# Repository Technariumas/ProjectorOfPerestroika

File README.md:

# ProjectorOfPerestroika
A wifi controlled old soviet flash light - a prop for a movie

To recreate:
 * Install ESP Arduino core (Tools/Board/Boards Manager...)
 * Install [Arduino ESP8266 filesystem uploader](https://github.com/esp8266/arduino-esp8266fs-plugin)

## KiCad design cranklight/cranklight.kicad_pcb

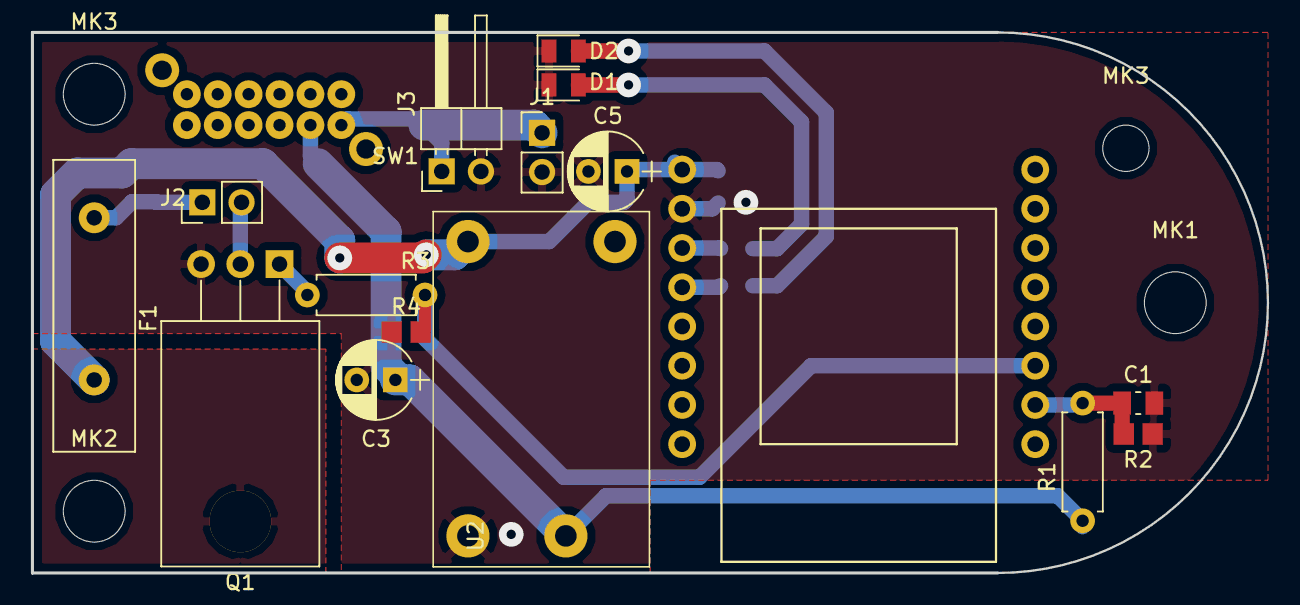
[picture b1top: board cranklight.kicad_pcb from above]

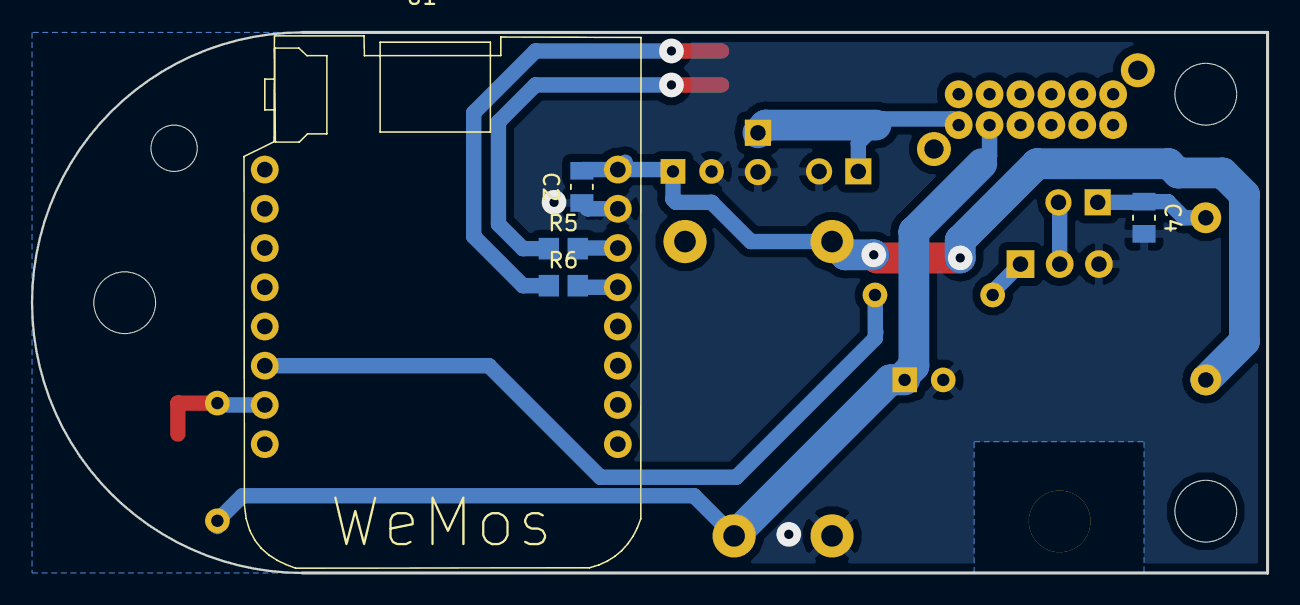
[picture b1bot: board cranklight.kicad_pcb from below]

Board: 2 copper layers, 80.0 x 35.0 mm, 25 parts (5 on the bottom side), 13 nets.

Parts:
C1, C2, C4: 1u; C_0805_2012Metric_Pad1.15x1.50mm_HandSolder
C3, C5: CP; CP_Radial_D5.0mm_P2.50mm
D1: GREEN; LED_0805_2012Metric
D2: RED; LED_0805_2012Metric
F1: Polyfuse; Fuse_Littelfuse-LVR100
J1: Battery; Pin_Header_Straight_1x02_Pitch2.54mm
J2: Bulb socket; Pin_Header_Straight_1x02_Pitch2.54mm
J3: Charge; Pin_Header_Angled_1x02_Pitch2.54mm
MK1, MK2, MK3, MK3#2: Mounting_Hole; MountingHole_3.7mm
Q1: Q_NMOS_GDS; TO-220-3_Horizontal
R1: 300k; R_Axial_DIN0207_L6.3mm_D2.5mm_P7.62mm_Horizontal
R2, R4: 100k; R_0805_2012Metric_Pad1.33x1.40mm_HandSolder
R3: 160; R_Axial_DIN0207_L6.3mm_D2.5mm_P7.62mm_Horizontal
R5, R6: 1k; R_0805_2012Metric_Pad1.33x1.40mm_HandSolder
SW1: SW_4PDT; 4PDT
U1: WeMos_mini; D1_mini_board
U2: PTN04050CAD; PTN04050

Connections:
+5V: C2.1, C5.1, F1.2, U1.1, U2.4
+BATT: J1.1, J3.1, SW1.12
GND: C1.2, C2.2, C3.2, C4.2, C5.2, D1.1, D2.1, J1.2, J3.2, Q1.3, R2.1, R4.1, U1.2, U2.1
unnamed: C1.1, R1.1, R2.2, U1.10
unnamed: C4.1, F1.1, J2.1
unnamed: D1.2, R5.1
unnamed: D2.2, R6.1
unnamed: J2.2, Q1.2
unnamed: Q1.1, R3.1
unnamed: R3.2, R4.2, U1.11
unnamed: R5.2, U1.3
unnamed: R6.2, U1.4
VCC: C3.1, R1.2, SW1.11, U2.2

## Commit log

2018-03-19 Initial commit, everything works
2018-03-19 Add some documentation about tools
2018-05-02 blink version for demo, files reshuffled
2018-05-02 Preheat after startup to avoid overstressing the battery (cold bulb resistance is very low, turning it fully on will cause battery protection circuit to hickup). Consider leaving on preheat in the lo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
2018-05-22 before state machine, three buttons
2018-05-22 state machine, enabled controls
2018-05-22 with blink rate param
2018-06-11 Add board files for small cranklight
2018-06-18 Add fixes: move PTC, add charging connector, use switch as a simple switch
2018-06-18 Add a simple test script for cranklight
2018-06-26 low battery warning
2018-06-26 D1 pin
2018-06-27 separate file for cranklight, simulated data
2018-06-27 separate sources, file reshuffle
2018-06-27 attempt to read from file
2018-06-27 play/pause/off
2018-06-27 pseudorandom sequences for pause and off cases
2018-06-28 rescaled analogwrite
2018-06-28 Voltage level, min brightness control, before adding random delay
2018-06-29 randomizer
2018-06-29 random blinking params
2018-06-29 setting load via JSON
2018-06-29 write to SPIFFS via JSON, test
2018-06-29 save and load presets
2018-06-30 before send/receive settings via JSON
2018-06-30 preset loading
2018-07-02 battery voltage indicator, websocket connection alert
2018-07-02 WIFI ssid works, failed due to short password
2018-07-03 Don't try to connect to WIFI as we are AP
2018-07-03 Add indication LEDS, add indication upon WiFi connect/disconnect
2018-07-03 flashing, voltage read test
2018-07-03 Some defensive coding - avoid creating objects and variables inside of functions to avoid working the stack and potentially allocating heap
2018-07-03 WiFi settings file
2018-07-03 More on defensive coding - reuse JsonBuffers as much as possible, remove one more dynamic buffer usage, load settings upon websocket connect, load settings upon system start
2018-07-03 Revert "Merge branch 'master' of github.com:Technariumas/ProjectorOfPerestroika"
    This reverts commit 15df6aaded9b8dc48269cf031f87443d8a172d73, reversing
    changes made to db87b0c735bae324813759881bcc5720fb8c6f46.
2018-07-03 no digitalWrite, lots of prints
2018-07-03 Add WEBSOCKETS_SERVER_CLIENT_MAX def as master of websockets lib allows to define it outside
2018-07-03 load WiFi settings from file
2018-07-03 sensible settings, CSS for tablet/mobile
2018-07-03 less Serial.print
2018-07-03 copy paste from cranklight, before rewriting
2018-07-03 JS error, voltage vs. val, check
2018-07-03 large flashlight, works
2018-07-03 fixed dimmer preset
2018-07-03 PWM duty cycle scaling
2018-07-04 voltage factor constants
2018-07-04 last fixes
2018-07-04 Don't increase PWM frequency as this causes various bugs
2018-07-10 18k analog write frequency
2018-07-11 fixed setting load bug
2018-07-11 websocket disconnection handling
2018-07-12 single WiFi connection per device
2018-07-12 Fade in/Fade out state machine
2018-07-13 fade button, play/pause single button
2018-07-13 JS debounce, brightness reset to zero before fadein
2018-07-13 fade in/out controls
2018-07-13 debounce all inputs
2018-07-13 time step parameters, frequency change
2018-07-13 wording
2018-07-13 save settings
2018-08-01 attempt at reconnecting
2018-08-02 reconnecting WS, dark at fadeout
2018-08-04 set IPs, fix fadeout blink bug
